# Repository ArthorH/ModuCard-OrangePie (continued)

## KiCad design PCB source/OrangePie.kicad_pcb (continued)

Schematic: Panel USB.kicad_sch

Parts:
C55: 100nF; C_0402; Voltage Rated 16V; Tolerance ±10%; Part CL05B104KO5NNNC; LCSC C1525
C56: 10uF; C_0805; Voltage Rated 50V; Tolerance ±10%; Part GRM21BR61H106KE43L; LCSC C440198
J5: USB_C_Receptacle_USB2.0_16P; USB_C_Receptacle_GCT_USB4105-xx-A_16P_TopMnt_Horizontal
R27, R28: 5.1kΩ; R_0402; Overload Voltage (Max) 50V; Tolerance ±1%; Part 0402WGF5101TCE; LCSC C25905
R29, R30: 22Ω; R_0402; Overload Voltage (Max) 50V; Tolerance ±1%; Part 0402WGF220JTCE; LCSC C25092
R31: 1kΩ; R_0402; Overload Voltage (Max) 50V; Tolerance ±1%; Part 0402WGF1001TCE; LCSC C11702
U402: TPD2E2U06DCK; SOT-323_SC-70

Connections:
/CH340_DEBUG/FRONT_PANEL.D+: R30.2, U402.1; also elsewhere on the board
/CH340_DEBUG/FRONT_PANEL.D-: R29.2, U402.2; also elsewhere on the board
/Panel USB/VBUS_IN: C56.1, J5.A4 (VBUS), J5.A9 (VBUS), J5.B4 (VBUS), J5.B9 (VBUS)
GND: C55.2, C56.2, J5.A1 (GND), J5.A12 (GND), J5.B1 (GND), J5.B12 (GND), R27.2, R28.2, R31.2, U402.3; also elsewhere on the board
unnamed: J5.A5 (CC1), R28.1
unnamed: J5.B5 (CC2), R27.1
unnamed: J5.A6 (D+), J5.B6 (D+), R30.1
unnamed: J5.A7 (D-), J5.B7 (D-), R29.1
unnamed: C55.1, J5.S1 (SHIELD), R31.1

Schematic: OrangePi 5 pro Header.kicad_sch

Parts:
C6: 10uF; C_1206; Voltage Rated 50V; Tolerance ±10%; Part CL31A106KBHNNNE; LCSC C13585
J2: Orange pi 5 pro; Orange Pi 5 pro
R40: 20kΩ; R_0402; Overload Voltage (Max) 50V; Tolerance ±1%; Part 0402WGF2002TCE; LCSC C25765
R41: 10kΩ; R_0402; Overload Voltage (Max) 50V; Tolerance ±1%; Part 0402WGF1002TCE; LCSC C25744
R44, R45: 22Ω; R_0402; Overload Voltage (Max) 50V; Tolerance ±1%; Part 0402WGF220JTCE; LCSC C25092

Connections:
+5V: C6.1, J2.1 (5V), J2.2 (5V); also elsewhere on the board
/5v buck/Pgood: R40.1; also elsewhere on the board
/Audio Codec/DAC reset: J2.14 (GPIO1_A3/I2C4_SCL/PWM1/SPI4_CS0); also elsewhere on the board
/CAN pwr sw/CAN_POWER_ON: J2.9 (GPIO1_A0/UART6_RX/SPI4_MISO); also elsewhere on the board
/CH340_DEBUG/UART_DEBUG.RX: J2.5 (GPIO0_B6/UART2_RX); also elsewhere on the board
/CH340_DEBUG/UART_DEBUG.TX: J2.4 (GPIO0_B5/UART2_TX); also elsewhere on the board
/Can Transiver/CAN_TR.RXD: J2.35 (GPIO4_B2/PWM14/CAN1_RX); also elsewhere on the board
/Can Transiver/CAN_TR.TXD: J2.34 (GPIO4_B3/PWM15/CAN1_TX); also elsewhere on the board
/DIN41612 connector/USB_DEBUG.D+: R44.2; also elsewhere on the board
/DIN41612 connector/USB_DEBUG.D-: R45.2; also elsewhere on the board
/FAN controller/FAN_PWM: J2.6 (GPIO1_A7/PWM3); also elsewhere on the board
/OrangePi 5 pro Header/ON OFF BTN: J2.26 (GPIO1_A4); also elsewhere on the board
/OrangePi 5 pro Header/STATUS LED: J2.11 (GPIO1_B0); also elsewhere on the board
/OrangePi 5 pro Header/USB_OUT.D+: J2.48 (USB20_DP3); also elsewhere on the board
/OrangePi 5 pro Header/USB_OUT.D-: J2.47 (USB20_DM3); also elsewhere on the board
/OrangePi 5 pro Header/USB_SBCF.D+: J2.43 (USB20_DP4), R44.1
/OrangePi 5 pro Header/USB_SBCF.D-: J2.44 (USB20_DM4), R45.1
/OrangePi 5 pro Header/USER BUTTON: J2.25 (GPIO1_A6); also elsewhere on the board
/OrangePi 5 pro Header/USER LED 1: J2.24 (GPIO1_D7/I2C8_SDA/PWM15)
/OrangePi 5 pro Header/USER LED 2: J2.23 (GPIO4_A7/I2C5_SDA)
/USB-CAN/NRST: J2.27 (GPIO1_A2/SPI4_CLK/PWM0/I2C4_SDA); also elsewhere on the board
GND: C6.2, J2.3 (GND), J2.7 (GND), J2.10 (GND), J2.15 (GND), J2.17 (GND), J2.21 (GND), J2.28 (GND), J2.36 (GND), J2.41 (USB_GND), J2.42 (USB_GND), J2.49 (USB_GND), R41.2; also elsewhere on the board
unnamed: J2.22 (GPIO4_A6/UART3_RX/I2C5_SCL), R40.2, R41.1

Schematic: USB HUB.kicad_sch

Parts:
C45, C47: 10uF; C_0402; Voltage Rated 6.3V; Tolerance ±20%; Part CL05A106MQ5NUNC; LCSC C15525
C46: 1uF; C_0402; Voltage Rated 25V; Tolerance ±10%; Part CL05A105KA5NQNC; LCSC C52923
U10: CH334R; QSOP-16_3.9x4.9mm_P0.635mm
Y1: 12MHz; Crystal_SMD_3225-4Pin_3.2x2.5mm

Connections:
+5V: C47.1, U10.12 (V5); also elsewhere on the board
/Audio Codec/USB_AUDIO.D+: U10.4 (DP3); also elsewhere on the board
/Audio Codec/USB_AUDIO.D-: U10.3 (DM3); also elsewhere on the board
/OrangePi 5 pro Header/USB_OUT.D+: U10.11 (DPU); also elsewhere on the board
/OrangePi 5 pro Header/USB_OUT.D-: U10.10 (DMU); also elsewhere on the board
/USB HUB/USB3.D+: U10.6 (DP2)
/USB HUB/USB3.D-: U10.5 (DM2)
/USB HUB/USB4.D+: U10.8 (DP1)
/USB HUB/USB4.D-: U10.7 (DM1)
/USB HUB/USB_CAN.D+: U10.2 (DP4); also elsewhere on the board
/USB HUB/USB_CAN.D-: U10.1 (DM4); also elsewhere on the board
GND: C45.2, C46.2, C47.2, U10.14 (GND), Y1.2, Y1.4; also elsewhere on the board
unnamed: C45.1, C46.1, U10.13 (VDD33)
unnamed: U10.16 (XI), Y1.1
unnamed: U10.15 (XO), Y1.3

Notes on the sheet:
HUB IC

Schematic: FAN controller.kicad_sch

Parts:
C49: 10uF; C_1206; Voltage Rated 50V; Tolerance ±10%; Part CL31A106KBHNNNE; LCSC C13585
D4: 1N4002W; D_SOD-123FL; Forward Voltage (Vf@If) 1V@1.0A; Reverse Voltage (Vr) 100V; Part 1N4002W; LCSC C18199086
M1: Fan; JST_XH_B2B-XH-AM_1x02_P2.50mm_Vertical
Q4: AO3400A; Q_SOT-23; Part AO3400A; LCSC C20917
R23: 0Ω; R_0402; Overload Voltage (Max) 50V; Tolerance ±1%; Part 0402WGF0000TCE; LCSC C17168
R24: 0Ω; R_0402; Overload Voltage (Max) 50V; Tolerance ±1%; Part 0402WGF0000TCE; LCSC C17168; not fitted
R25: 1.5kΩ; R_0402; Overload Voltage (Max) 50V; Tolerance ±1%; Part 0402WGF1501TCE; LCSC C25867
R26: 10kΩ; R_0402; Overload Voltage (Max) 50V; Tolerance ±1%; Part 0402WGF1002TCE; LCSC C25744

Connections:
+5V: R24.2; also elsewhere on the board
/5v buck/V_{IN}: R23.2; also elsewhere on the board
/FAN controller/FAN_PWM: R25.1; also elsewhere on the board
GND: C49.2, Q4.2 (S), R26.1; also elsewhere on the board
unnamed: C49.1, D4.1, M1.1 (+), R23.1, R24.1
unnamed: D4.2, M1.2 (-), Q4.3 (D)
unnamed: Q4.1 (G), R25.2, R26.2

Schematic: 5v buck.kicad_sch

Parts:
C7, C9, C11: 100nF; C_0402; Voltage Rated 50V; Tolerance ±10%; Part CL05B104KB54PNC; LCSC C307331
C8, C12, C13, C58, C61, C62, C63: 10uF; C_0603; Voltage Rated 10V; Tolerance ±10%; Part CL10A106KP8NNNC; LCSC C19702
C10, C57: 22uF; C_0805; Voltage Rated 25V; Tolerance ±20%; Part CL21A226MAQNNNE; LCSC C45783
C14: 1uF; C_0402; Voltage Rated 25V; Tolerance ±10%; Part CL05A105KA5NQNC; LCSC C52923
C15: 4.7uF; C_0402; Voltage Rated 10V; Tolerance ±20%; Part CL05A475MP5NRNC; LCSC C23733
JP1: Solder Jumper; SolderJumper-2_P1.3mm_Open_RoundedPad1.0x1.5mm
L2: 1uH; L_Bourns_SRP7028A_7.3x6.6mm; MPN CENKER CKST1004-1uH/M-B; LCSC C3002679
R1: 2.2kΩ; R_0402; Overload Voltage (Max) 50V; Tolerance ±1%; Part 0402WGF2201TCE; LCSC C25879
R2, R6: 10kΩ; R_0402; Overload Voltage (Max) 50V; Tolerance ±1%; Part 0402WGF1002TCE; LCSC C25744
R3: 73k2; R_0402; Overload Voltage (Max) 50V; Tolerance ±1%; Part 0402WGF0000TCE; LCSC C17168
R4, R7, R36: 499k; R_0402; Overload Voltage (Max) 50V; Tolerance ±1%; Part 0402WGF0000TCE; LCSC C17168
R32: 20kΩ; R_0402; Overload Voltage (Max) 50V; Tolerance ±1%; Part 0402WGF2002TCE; LCSC C25765
U2: SIC431AED-T1-GE3; REGULATOR_SIC431AED-T1-GE3; MPN SIC431AED-T1-GE3

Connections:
/5v buck/5V_BOOT: C7.1, U2.23 (BOOT)
/5v buck/5V_EN: C9.1, R1.1, R32.2, U2.19 (EN)
/5v buck/5V_FB: R2.1, R3.2, U2.17 (FB)
/5v buck/5V_MODE1: R4.2, R36.1, U2.21 (MODE1)
/5v buck/5V_MODE2: R7.1, U2.20 (MODE2)
/5v buck/5V_OUT: C8.1, C12.1, C13.1, C58.1, C61.1, C62.1, C63.1, JP1.1 (A), L2.2, R3.1, R6.1, U2.18 (V_{OUT})
/5v buck/5V_PHASE: C7.2, U2.24 (PHASE)
/5v buck/5V_SW: L2.1, U2.5 (SW), U2.6 (SW), U2.7 (SW), U2.8 (SW), U2.9 (SW), U2.9.1 (SW)
/5v buck/5V_VDD: C14.1, R4.1, U2.15 (V_{DD})
/5v buck/5V_VDRV: C15.1, U2.12 (V_{DRV})
/5v buck/BUCK_OUT: JP1.2 (B); also elsewhere on the board
/5v buck/Pgood: R6.2, U2.14 (P_{GOOD}); also elsewhere on the board
/5v buck/V_{IN}: C10.1, C11.1, C57.1, R32.1, U2.1 (V_{IN}), U2.2 (V_{IN}), U2.22 (V_{IN}), U2.26 (V_{IN}); also elsewhere on the board
GND: C8.2, C9.2, C10.2, C11.2, C12.2, C13.2, C14.2, C15.2, C57.2, C58.2, C61.2, C62.2, C63.2, R1.2, R2.2, R7.2, R36.2, U2.3 (P_{GND}), U2.4 (P_{GND}), U2.13 (P_{GND}), U2.16 (A_{GND}), U2.25 (A_{GND}), U2.27 (P_{GND}), U2.27_1 (GND), U2.27_2 (GND); also elsewhere on the board

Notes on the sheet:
Sets UVLO to 10.8V
Modified by Artem H for JLCPCB fabhouse capabilities
~{ok}
Copied from ANTMICRO opensource hardware poral check out other designs at https://openhardware.antmicro.com
V_{OUT} = 0.6*(R_{FB_H}+R_{FB_L})/R_{FB_L}
5V @8A
buck off
V_{OUT} = 0.6*(73k2+10k)/10k = 4.992[V]
R_{FB_H} = (R_{FB_L}(V_{OUT}-0.6))/0.6

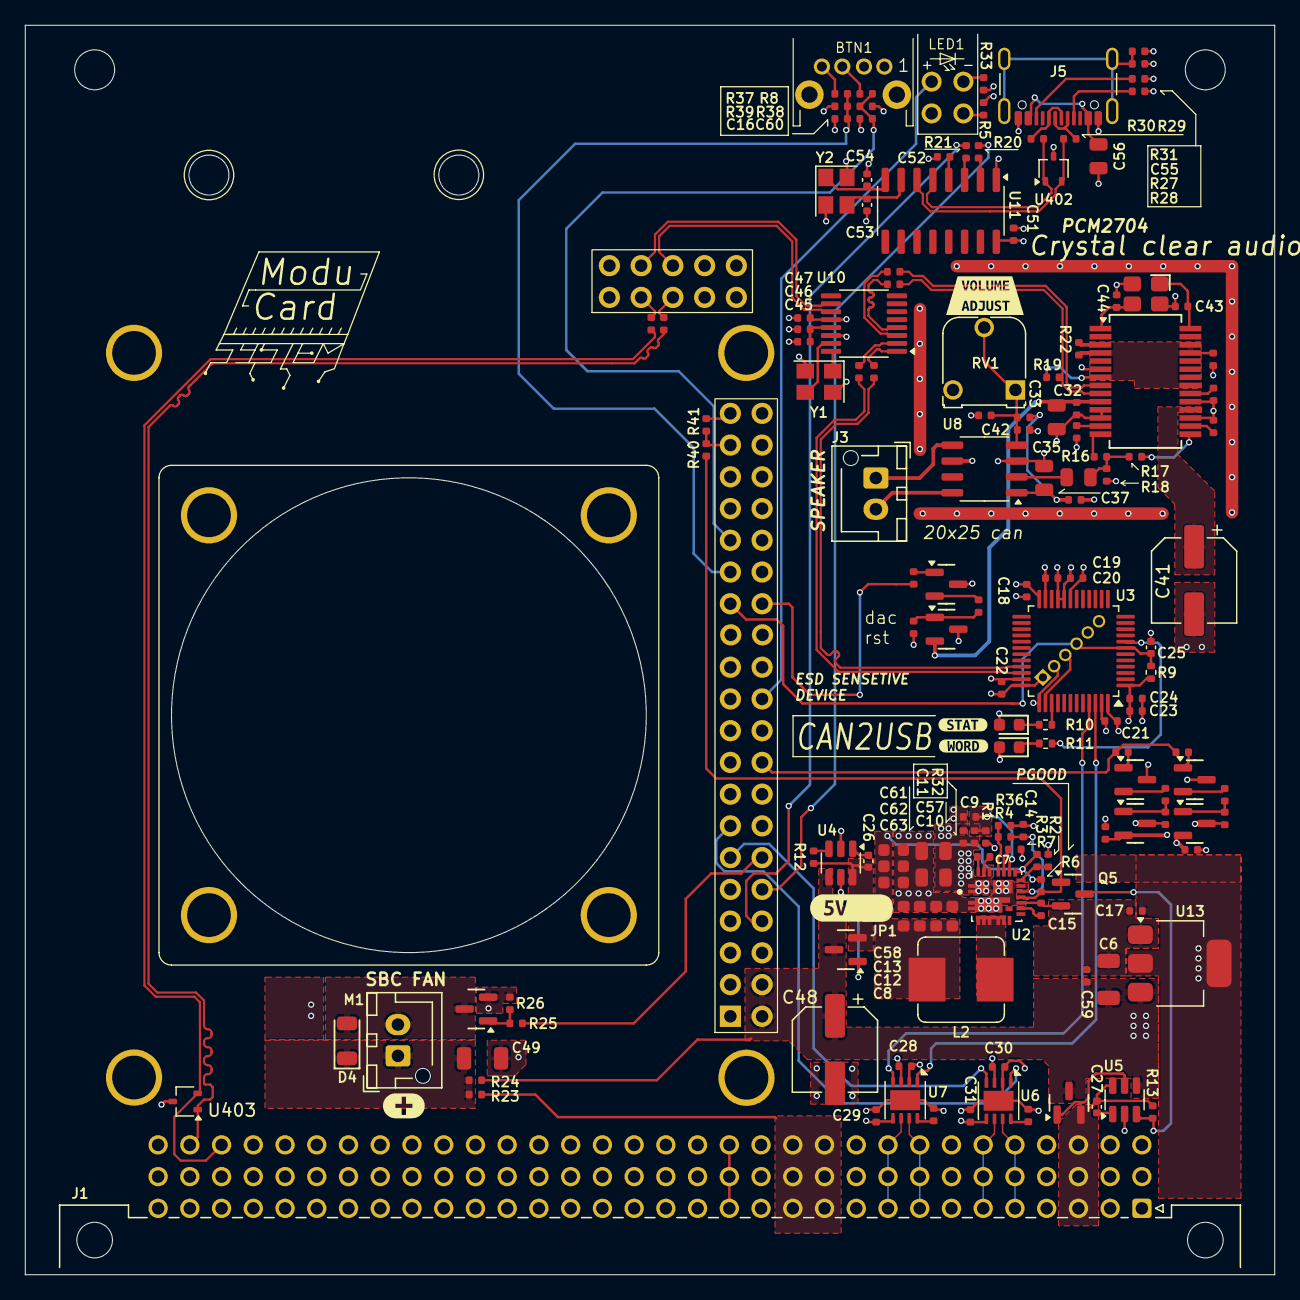
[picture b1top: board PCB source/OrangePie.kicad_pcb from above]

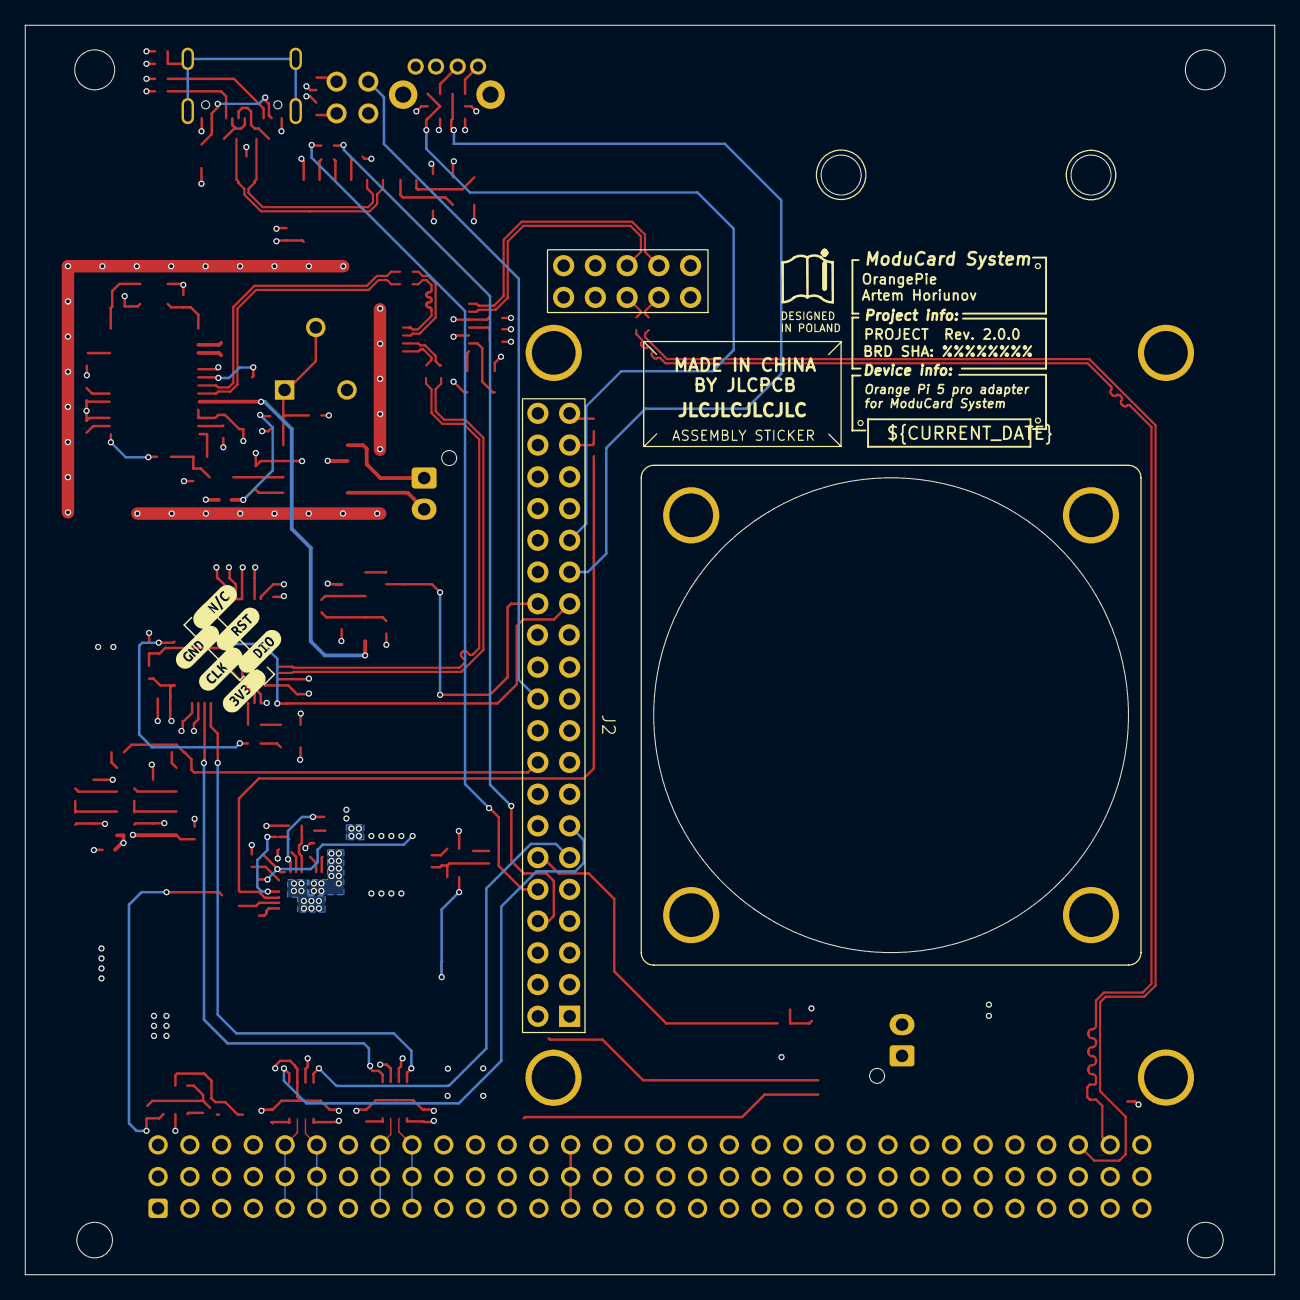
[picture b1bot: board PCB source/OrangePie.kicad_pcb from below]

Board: 4 copper layers, 100.0 x 100.0 mm, 166 parts (8 on the bottom side), 114 nets.

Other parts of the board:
kibuzzard-67B7B9BD: G***; kibuzzard-67B7B9BD
kibuzzard-67B7B9C6: G***; kibuzzard-67B7B9C6
kibuzzard-67B7BB29: G***; kibuzzard-67B7BB29
kibuzzard-67B7BD37: G***; kibuzzard-67B7BD37
kibuzzard-67B7BFDD: G***; kibuzzard-67B7BFDD
kibuzzard-67B7C21F: G***; kibuzzard-67B7C21F
kibuzzard-67B7C241: G***; kibuzzard-67B7C241
kibuzzard-67B62470: G***; kibuzzard-67B62470
kibuzzard-68D4781A: G***; kibuzzard-68D4781A
kibuzzard-68D47809: G***; kibuzzard-68D47809
kibuzzard-68D47811: G***; kibuzzard-68D47811

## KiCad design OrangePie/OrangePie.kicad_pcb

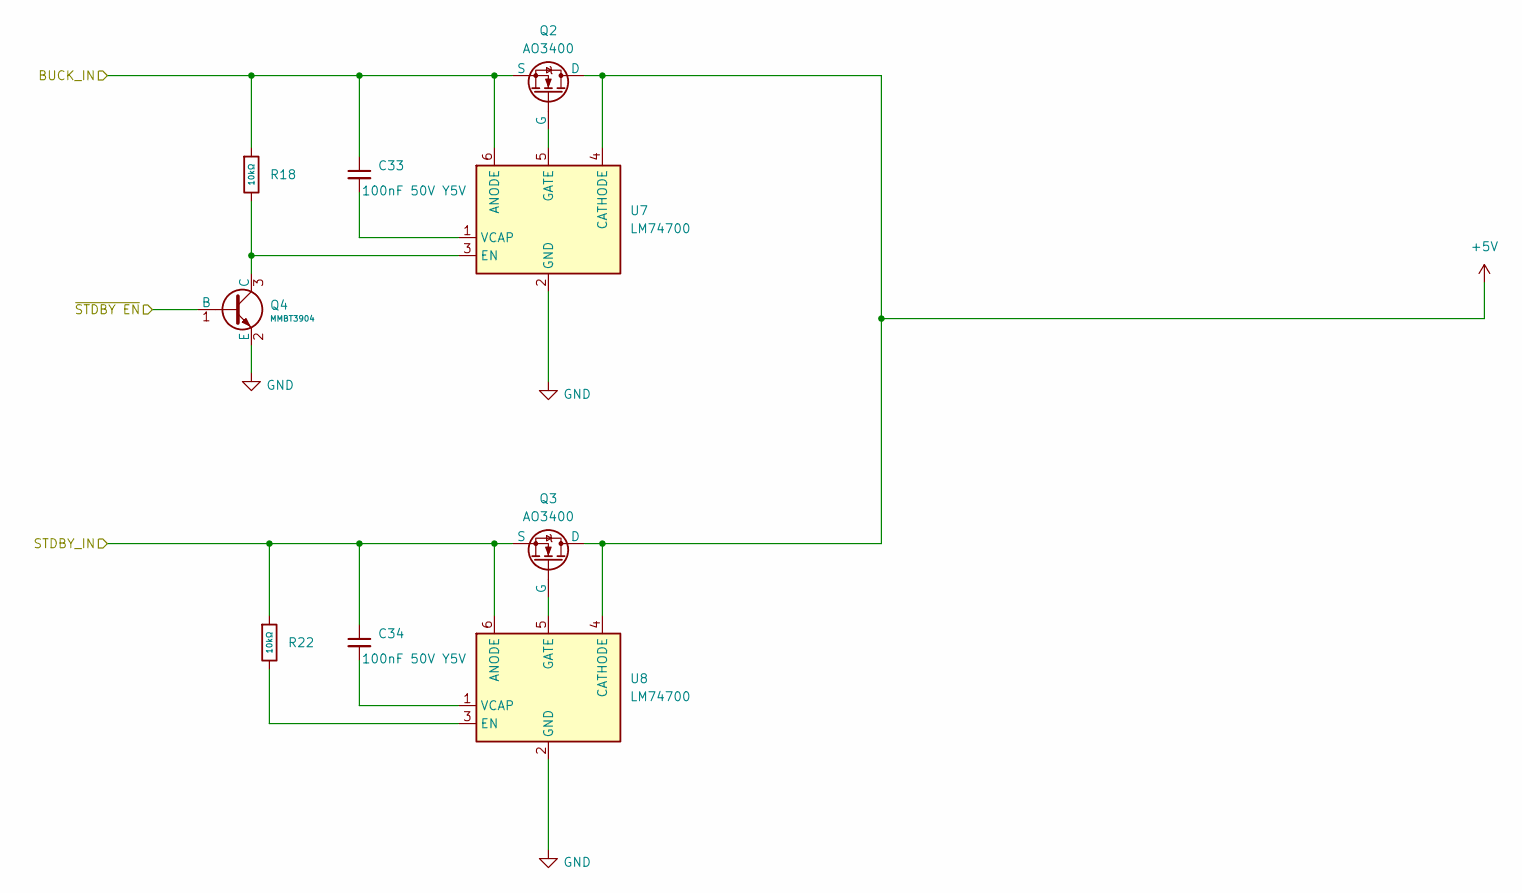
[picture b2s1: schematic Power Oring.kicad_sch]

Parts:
C33, C34: 100nF 50V Y5V; C_0402_1005Metric
Q2, Q3: AO3400; SOT-23
Q4: MMBT3904; Q_SOT-23; Part MMBT3904; LCSC C7420353
R18, R22: 10kΩ; R_0402; Overload Voltage (Max) 50V; Tolerance ±1%; Part 0402WGF1002TCE; LCSC C25744
U7, U8: LM74700; SOT-23-6

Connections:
+5V: Q2.2 (D), Q3.2 (D), U7.4 (CATHODE), U8.4 (CATHODE); also elsewhere on the board
/5v buck/5V_OUT: C33.1, Q2.3 (S), Q4.1 (B), R18.1, U7.6 (ANODE); also elsewhere on the board
GND: Q4.2 (E), U7.2 (GND), U8.2 (GND); also elsewhere on the board
unnamed: Q2.1 (G), U7.5 (GATE)
unnamed: Q3.1 (G), U8.5 (GATE)
unnamed: Q4.3 (C), R18.2, U7.3 (EN)
unnamed: C33.2, U7.1 (VCAP)
unnamed: R22.2, U8.3 (EN)
unnamed: C34.2, U8.1 (VCAP)

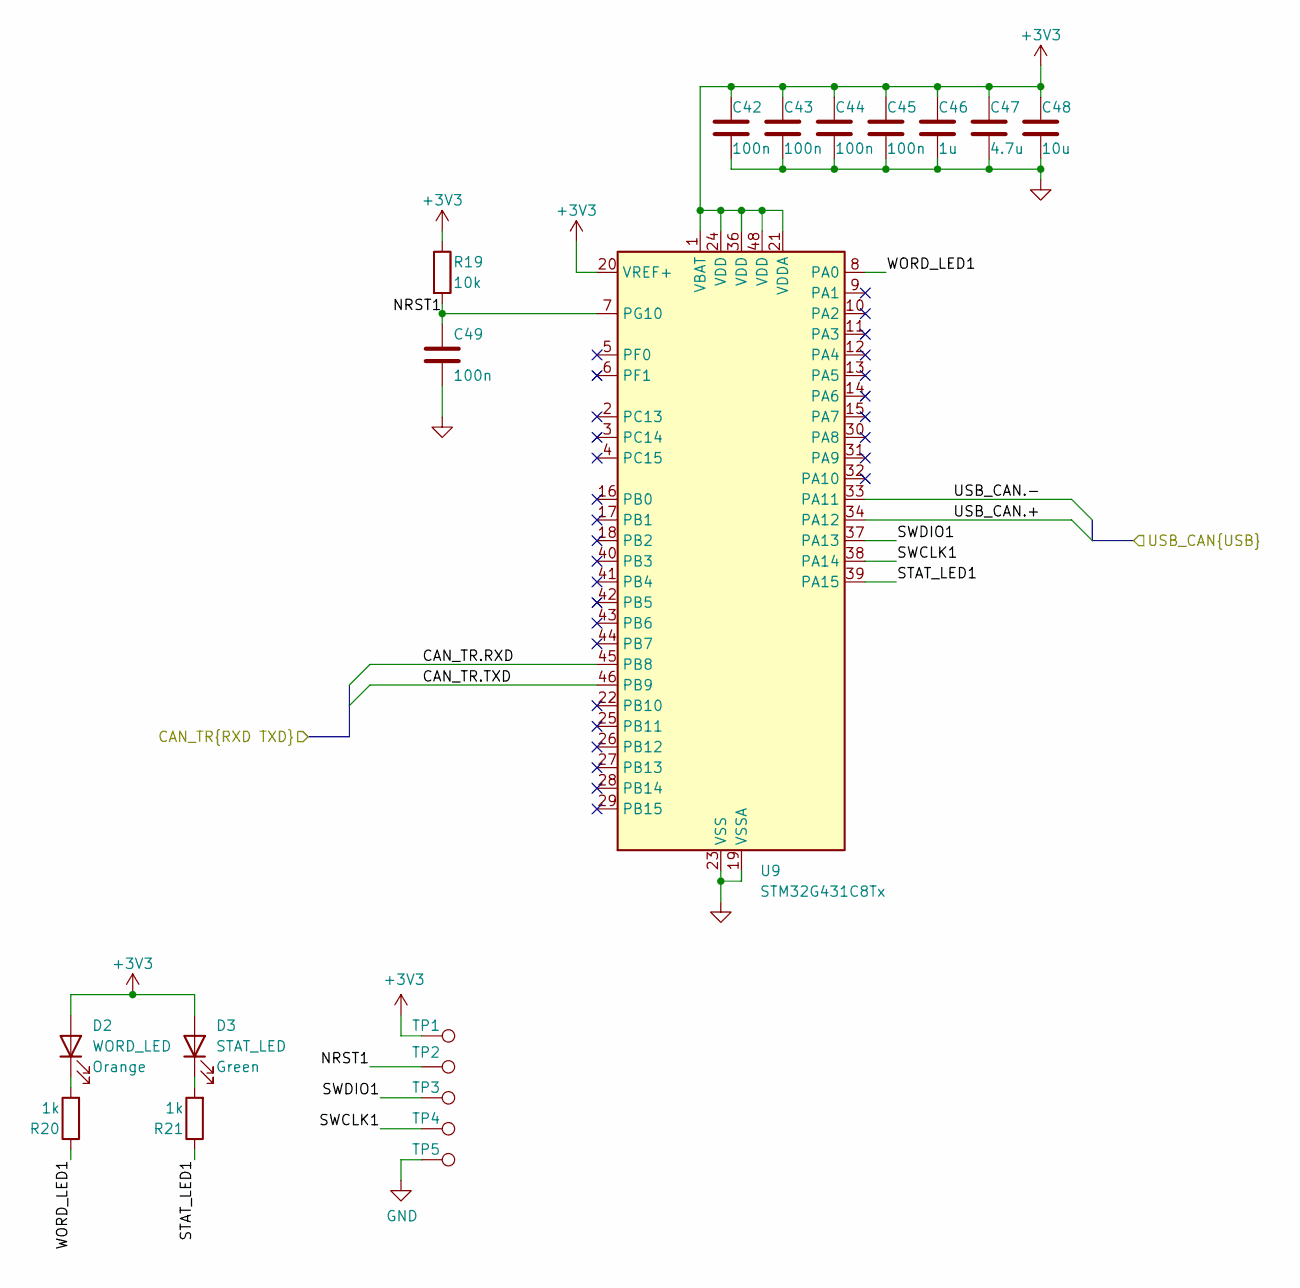
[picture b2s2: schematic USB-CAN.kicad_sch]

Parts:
C42, C43, C44, C45, C49: 100n; C_0402_1005Metric
C46: 1u; C_0603_1608Metric
C47: 4.7u; C_0603_1608Metric
C48: 10u; C_0805_2012Metric
D2: WORD_LED; D_0603_1608Metric
D3: STAT_LED; D_0603_1608Metric
R19: 10k; R_0402_1005Metric
R20, R21: 1k; R_0402_1005Metric
TP1, TP2, TP3, TP4, TP5: TestPoint_Pad_1.0x1.0mm
U9: STM32G431C8Tx; LQFP-48_7x7mm_P0.5mm

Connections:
+3V3: C42.1, C43.1, C44.1, C45.1, C46.1, C47.1, C48.1, D2.2 (A), D3.2 (A), R19.1, TP1.1, U9.1 (VBAT), U9.20 (VREF+), U9.21 (VDDA), U9.24 (VDD), U9.36 (VDD), U9.48 (VDD); also elsewhere on the board
/Can Transiver1/CAN_TR.RXD: U9.45 (PB8); also elsewhere on the board
/Can Transiver1/CAN_TR.TXD: U9.46 (PB9); also elsewhere on the board
/USB HUB/USB_CAN.+: U9.34 (PA12); also elsewhere on the board
/USB HUB/USB_CAN.-: U9.33 (PA11); also elsewhere on the board
/USB-CAN/NRST1: C49.1, R19.2, TP2.1, U9.7 (PG10)
/USB-CAN/STAT_LED1: R21.1, U9.39 (PA15)
/USB-CAN/SWCLK1: TP4.1, U9.38 (PA14)
/USB-CAN/SWDIO1: TP3.1, U9.37 (PA13)
/USB-CAN/WORD_LED1: R20.1, U9.8 (PA0)
GND: C42.2, C43.2, C44.2, C45.2, C46.2, C47.2, C48.2, C49.2, TP5.1, U9.19 (VSSA), U9.23 (VSS), U9.35 (VSS), U9.47 (VSS); also elsewhere on the board
unnamed: D2.1 (K), R20.2
unnamed: D3.1 (K), R21.2

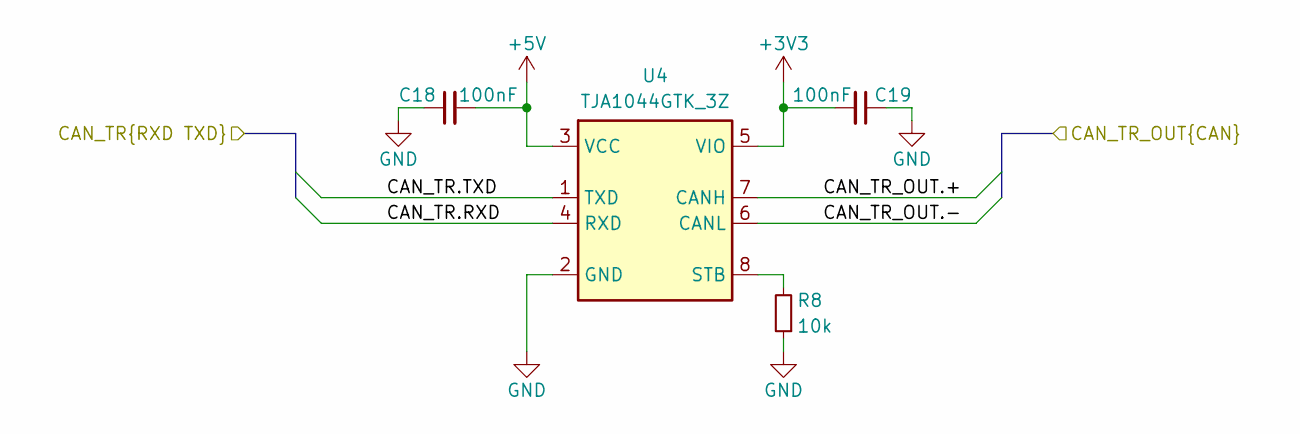
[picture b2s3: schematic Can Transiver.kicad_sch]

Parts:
C18, C19: 100nF; C_0402_1005Metric
R8: 10k; R_0402_1005Metric
U4: TJA1044GTK_3Z; HVSON-8-1EP_3x3mm_P0.65mm_EP1.6x2.4mm; Manufacturer_Part_Number TJA1044GTK/3Z

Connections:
+3V3: C19.2, U4.5 (VIO); also elsewhere on the board
+5V: C18.2, U4.3 (VCC); also elsewhere on the board
/Can Transiver/CAN_TR.RXD: U4.4 (RXD)
/Can Transiver/CAN_TR.TXD: U4.1 (TXD)
/Can Transiver/CAN_TR_OUT.+: U4.7 (CANH)
/Can Transiver/CAN_TR_OUT.-: U4.6 (CANL)
GND: C18.1, C19.1, R8.1, U4.2 (GND), U4.9 (EP); also elsewhere on the board
unnamed: R8.2, U4.8 (STB)

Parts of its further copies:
C20, C21: 100nF; C_0402_1005Metric
R9: 10k; R_0402_1005Metric
U5: TJA1044GTK_3Z; HVSON-8-1EP_3x3mm_P0.65mm_EP1.6x2.4mm; Manufacturer_Part_Number TJA1044GTK/3Z

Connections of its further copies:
+3V3: C21.2, U5.5 (VIO); also elsewhere on the board
+5V: C20.2, U5.3 (VCC); also elsewhere on the board
/Can Transiver1/CAN_TR.RXD: U5.4 (RXD); also elsewhere on the board
/Can Transiver1/CAN_TR.TXD: U5.1 (TXD); also elsewhere on the board
/Can Transiver1/CAN_TR_OUT.+: U5.7 (CANH)
/Can Transiver1/CAN_TR_OUT.-: U5.6 (CANL)
GND: C20.1, C21.1, R9.1, U5.2 (GND), U5.9 (EP); also elsewhere on the board
unnamed: R9.2, U5.8 (STB)

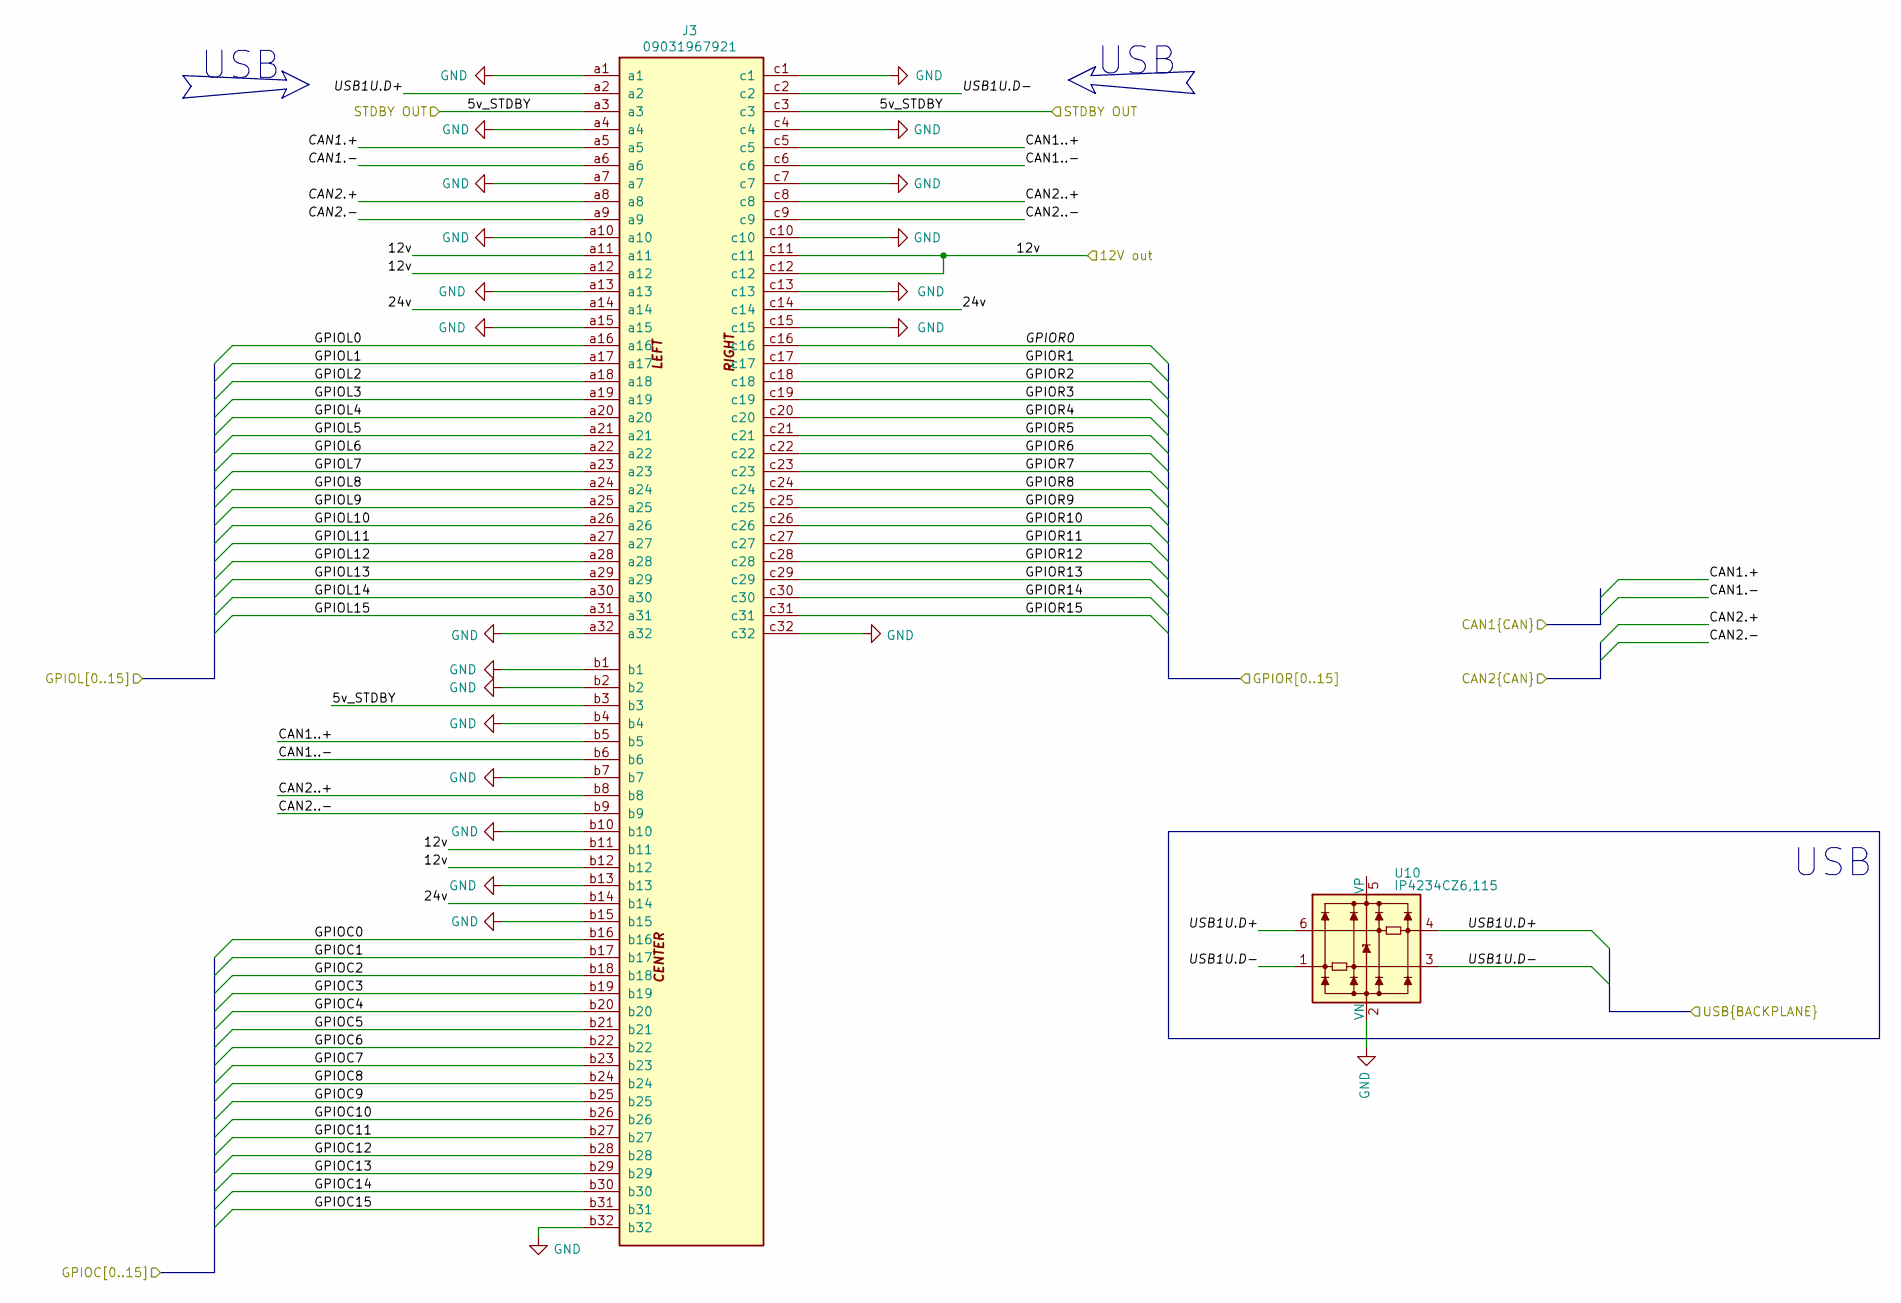
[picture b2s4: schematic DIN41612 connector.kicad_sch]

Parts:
J3: 09031967921; DIN41612_R_3x32_Female_Horizontal_THT; PARTREV D
U10: IP4234CZ6,115; SC-74-6_1.55x2.9mm_P0.95mm

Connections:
/DIN41612 connector/CAN1.+: J3.a5
/DIN41612 connector/CAN1.-: J3.a6
/DIN41612 connector/CAN1..+: J3.b5, J3.c5
/DIN41612 connector/CAN1..-: J3.b6, J3.c6
/DIN41612 connector/CAN2.+: J3.a8
/DIN41612 connector/CAN2.-: J3.a9
/DIN41612 connector/CAN2..+: J3.b8, J3.c8
/DIN41612 connector/CAN2..-: J3.b9, J3.c9
/DIN41612 connector/GPIOC0: J3.b16
/DIN41612 connector/GPIOC1: J3.b17
/DIN41612 connector/GPIOC2: J3.b18
/DIN41612 connector/GPIOC3: J3.b19
/DIN41612 connector/GPIOC4: J3.b20
/DIN41612 connector/GPIOC5: J3.b21
/DIN41612 connector/GPIOC6: J3.b22
/DIN41612 connector/GPIOC7: J3.b23
/DIN41612 connector/GPIOC8: J3.b24
/DIN41612 connector/GPIOC9: J3.b25
/DIN41612 connector/GPIOC10: J3.b26
/DIN41612 connector/GPIOC11: J3.b27
/DIN41612 connector/GPIOC12: J3.b28
/DIN41612 connector/GPIOC13: J3.b29
/DIN41612 connector/GPIOC14: J3.b30
/DIN41612 connector/GPIOC15: J3.b31
/DIN41612 connector/GPIOL0: J3.a16
/DIN41612 connector/GPIOL1: J3.a17
/DIN41612 connector/GPIOL2: J3.a18
/DIN41612 connector/GPIOL3: J3.a19
/DIN41612 connector/GPIOL4: J3.a20
/DIN41612 connector/GPIOL5: J3.a21
/DIN41612 connector/GPIOL6: J3.a22
/DIN41612 connector/GPIOL7: J3.a23
/DIN41612 connector/GPIOL8: J3.a24
/DIN41612 connector/GPIOL9: J3.a25
/DIN41612 connector/GPIOL10: J3.a26
/DIN41612 connector/GPIOL11: J3.a27
/DIN41612 connector/GPIOL12: J3.a28
/DIN41612 connector/GPIOL13: J3.a29
/DIN41612 connector/GPIOL14: J3.a30
/DIN41612 connector/GPIOL15: J3.a31
/DIN41612 connector/GPIOR0: J3.c16
/DIN41612 connector/GPIOR1: J3.c17
/DIN41612 connector/GPIOR2: J3.c18
/DIN41612 connector/GPIOR3: J3.c19
/DIN41612 connector/GPIOR4: J3.c20
/DIN41612 connector/GPIOR5: J3.c21
/DIN41612 connector/GPIOR6: J3.c22
/DIN41612 connector/GPIOR7: J3.c23
/DIN41612 connector/GPIOR8: J3.c24
/DIN41612 connector/GPIOR9: J3.c25
/DIN41612 connector/GPIOR10: J3.c26
/DIN41612 connector/GPIOR11: J3.c27
/DIN41612 connector/GPIOR12: J3.c28
/DIN41612 connector/GPIOR13: J3.c29
/DIN41612 connector/GPIOR14: J3.c30
/DIN41612 connector/GPIOR15: J3.c31
/DIN41612 connector/USB1U.D+: J3.a2, U10.4, U10.6
/DIN41612 connector/USB1U.D-: J3.c2, U10.1, U10.3
GND: J3.a1, J3.a4, J3.a7, J3.a10, J3.a13, J3.a15, J3.a32, J3.b1, J3.b2, J3.b4, J3.b7, J3.b10, J3.b13, J3.b15, J3.b32, J3.c1, J3.c4, J3.c7, J3.c10, J3.c13, J3.c15, J3.c32, U10.2 (VN); also elsewhere on the board

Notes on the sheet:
USB

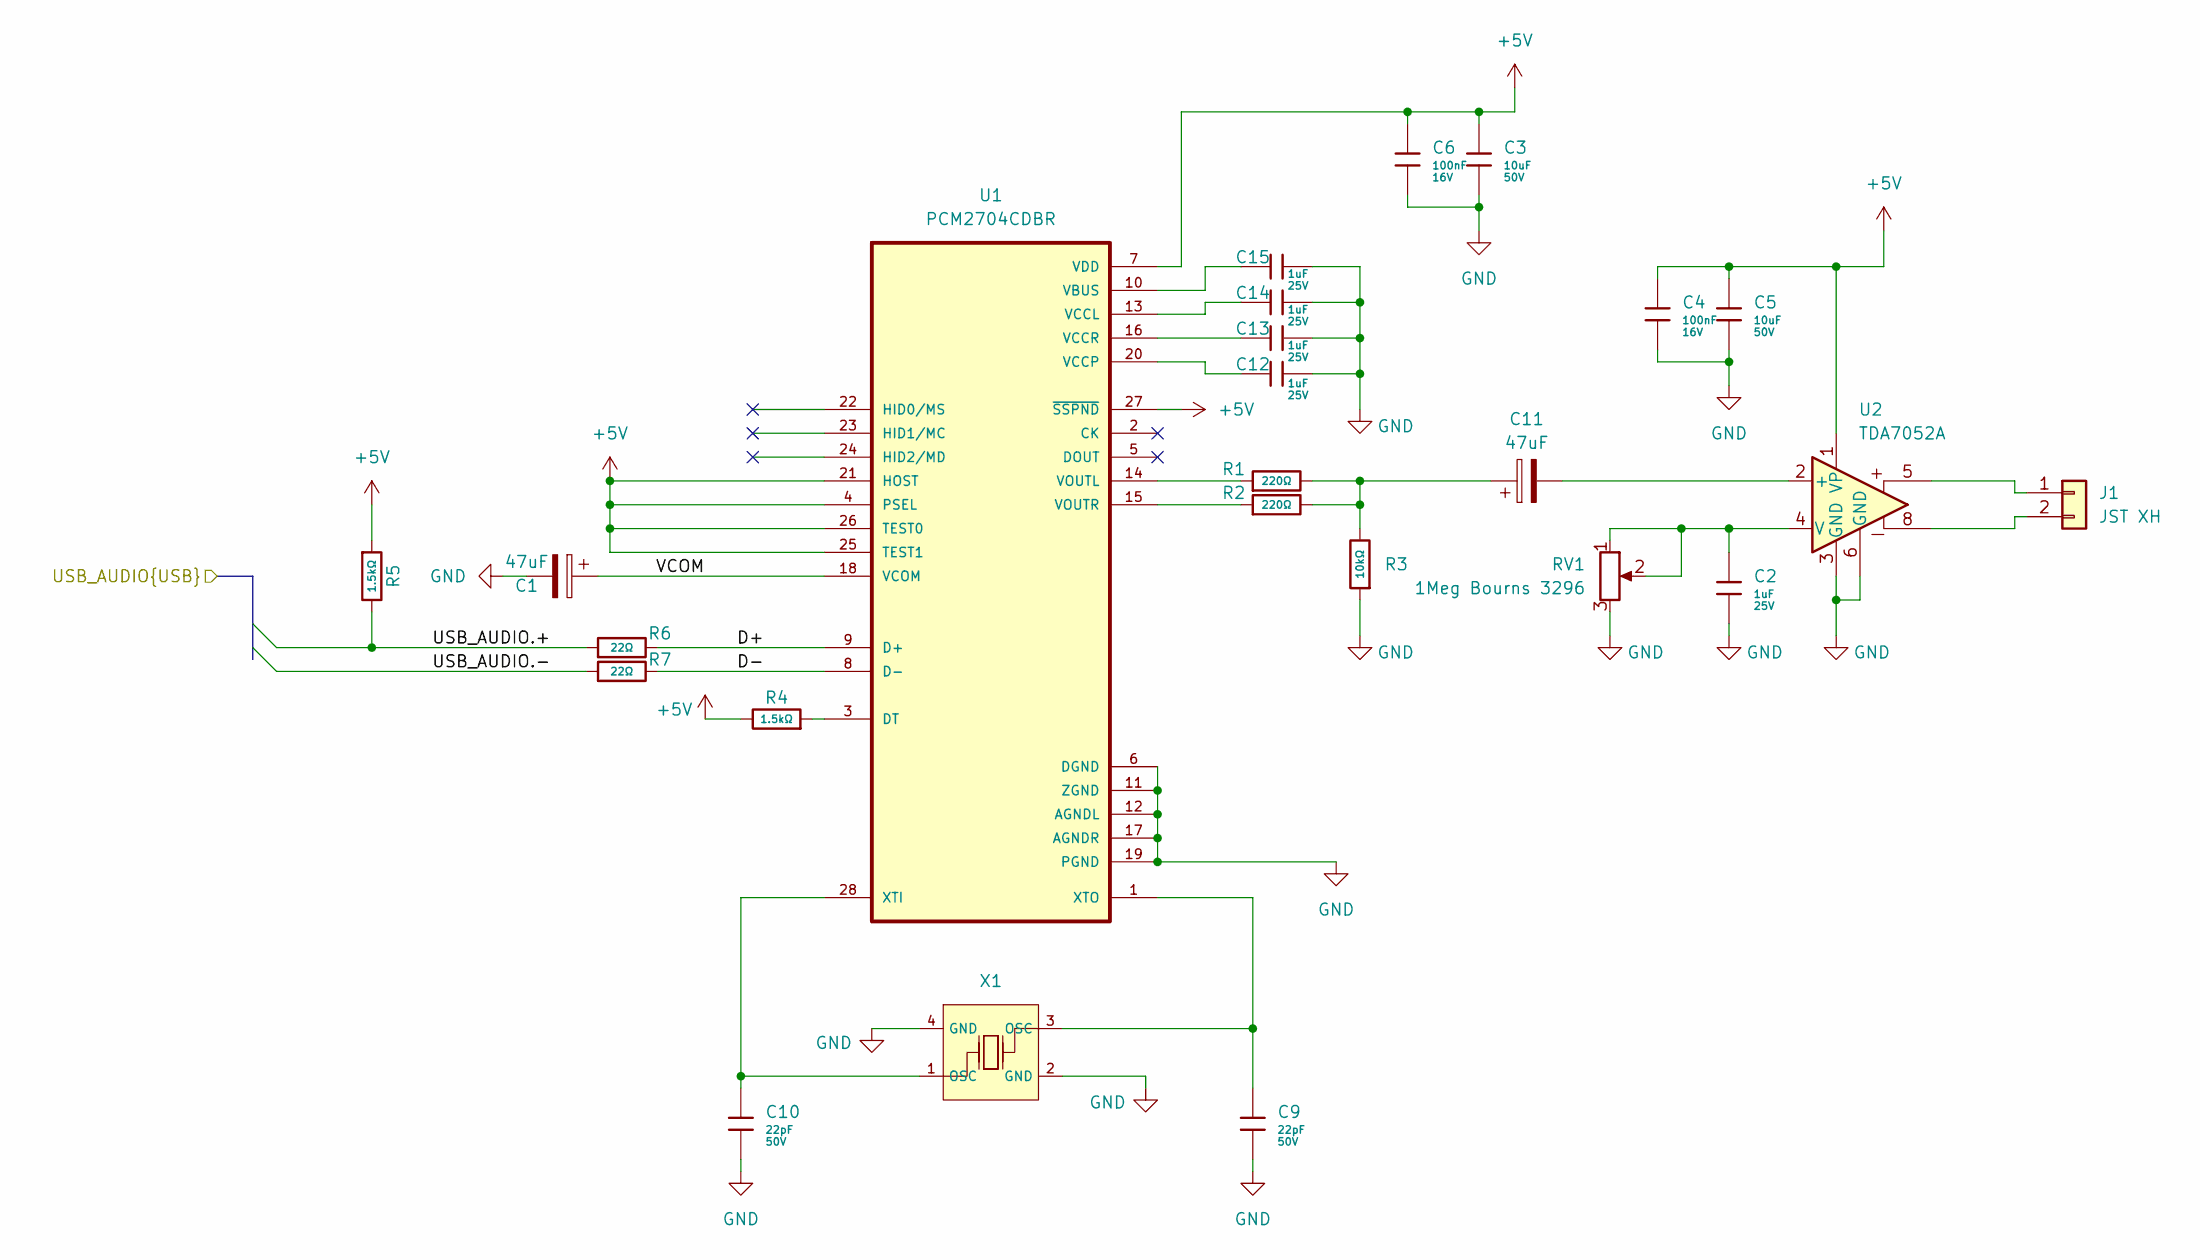
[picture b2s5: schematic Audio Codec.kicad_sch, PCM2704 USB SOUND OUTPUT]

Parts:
C1, C11: 47uF; CP_Elec_6.3x5.4; MPN VT1V470M0605; LCSC C90276
C2, C12, C13, C14, C15: 1uF; C_0402; Voltage Rated 25V; Tolerance ±10%; Part CL05A105KA5NQNC; LCSC C52923
C3, C5: 10uF; C_0805; Voltage Rated 50V; Tolerance ±10%; Part GRM21BR61H106KE43L; LCSC C440198
C4, C6: 100nF; C_0402; Voltage Rated 16V; Tolerance ±10%; Part CL05B104KO5NNNC; LCSC C1525
C9, C10: 22pF; C_0402; Voltage Rated 50V; Tolerance ±5%; Part 0402CG220J500NT; LCSC C1555
J1: JST XH; JST_XH_B2B-XH-AM_1x02_P2.50mm_Vertical
R1, R2: 220Ω; R_0402; Overload Voltage (Max) 50V; Tolerance ±1%; Part 0402WGF2200TCE; LCSC C25091
R3: 10kΩ; R_0402; Overload Voltage (Max) 50V; Tolerance ±1%; Part 0402WGF1002TCE; LCSC C25744
R4, R5: 1.5kΩ; R_0402; Overload Voltage (Max) 50V; Tolerance ±1%; Part 0402WGF1501TCE; LCSC C25867
R6, R7: 22Ω; R_0402; Overload Voltage (Max) 50V; Tolerance ±1%; Part 0402WGF220JTCE; LCSC C25092
RV1: 1Meg Bourns 3296; Potentiometer_Bourns_3296W_Vertical
U1: PCM2704CDBR; SOP65P780X200-28N
U2: TDA7052A
X1: X322512MSB4SI; CRYSTAL-SMD_4P-L3.2-W2.5-BL; Frequency Tolerance ±10ppm; Part X322512MSB4SI; LCSC C9002

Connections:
+5V: C3.2, C4.1, C5.2, C6.1, R4.2, R5.1, U1.4 (PSEL), U1.7 (VDD), U1.21 (HOST), U1.25 (TEST1), U1.26 (TEST0), U1.27 (~SSPND), U2.1 (VP); also elsewhere on the board
/Audio Codec/D+: R6.2, U1.9 (D+)
/Audio Codec/D-: R7.2, U1.8 (D-)
/Audio Codec/USB_AUDIO.+: R5.2, R6.1; also elsewhere on the board
/Audio Codec/USB_AUDIO.-: R7.1; also elsewhere on the board
/Audio Codec/VCOM: C1.1, U1.18 (VCOM)
GND: C1.2, C2.2, C3.1, C4.2, C5.1, C6.2, C9.2, C10.2, C12.2, C13.2, C14.2, C15.2, R3.1, RV1.3, U1.6 (DGND), U1.11 (ZGND), U1.12 (AGNDL), U1.17 (AGNDR), U1.19 (PGND), U2.3 (GND), U2.6 (GND), X1.2 (GND), X1.4 (GND); also elsewhere on the board
unnamed: C11.1, R1.2, R2.2, R3.2
unnamed: J1.1, U2.5
unnamed: J1.2, U2.8
unnamed: R4.1, U1.3 (DT)
unnamed: C15.1, U1.10 (VBUS)
unnamed: C14.1, U1.13 (VCCL)
unnamed: C12.1, U1.20 (VCCP)
unnamed: C13.1, U1.16 (VCCR)
unnamed: R1.1, U1.14 (VOUTL)
unnamed: R2.1, U1.15 (VOUTR)
unnamed: C10.1, U1.28 (XTI), X1.1 (OSC)
unnamed: C9.1, U1.1 (XTO), X1.3 (OSC)
unnamed: C11.2, U2.2 (+)
unnamed: C2.1, RV1.1, RV1.2, U2.4 (V)
